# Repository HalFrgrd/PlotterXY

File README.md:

# PlotterXY

- Mainly based on https://github.com/jamescarruthers/PlotteRXY.
- I am using a different main board, y-axis, z-axis. Parts found in onshape.

## How to use
- Open fluidnc in the browser. See https://github.com/HalFrgrd/PlotterXY/blob/main/Firmware/readme.md
- Home all the axes.
- Generate some gcode using vpype. See https://github.com/HalFrgrd/PlotterXY/blob/main/Software/readme.md
- Upload or copy it over to the sd card.
- Plot!

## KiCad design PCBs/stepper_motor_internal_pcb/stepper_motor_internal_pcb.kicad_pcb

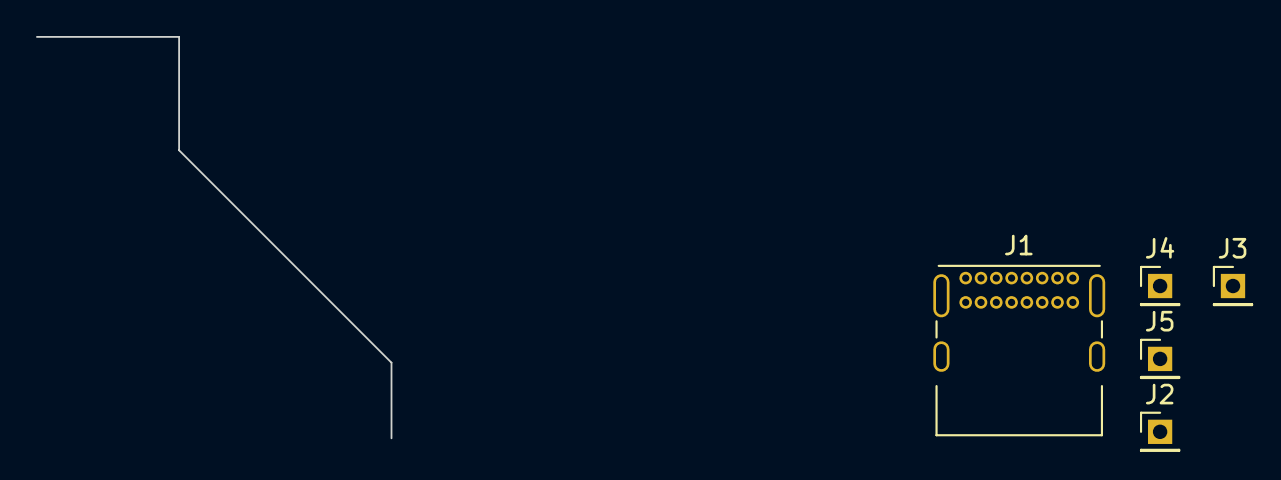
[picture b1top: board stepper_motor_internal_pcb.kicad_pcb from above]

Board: 2 copper layers, 5 parts (0 on the bottom side), 2 nets, no tracks yet.

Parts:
J1: USB_C_Receptacle_USB2.0; USB_C_Receptacle_GCT_USB4085
J2, J3, J4, J5: Conn_01x01_Female; PinHeader_1x01_P2.00mm_Vertical

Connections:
unnamed: J1.A1 (GND), J1.A12 (GND), J1.B1 (GND), J1.B12 (GND)
unnamed: J1.A4 (VBUS), J1.A9 (VBUS), J1.B4 (VBUS), J1.B9 (VBUS)

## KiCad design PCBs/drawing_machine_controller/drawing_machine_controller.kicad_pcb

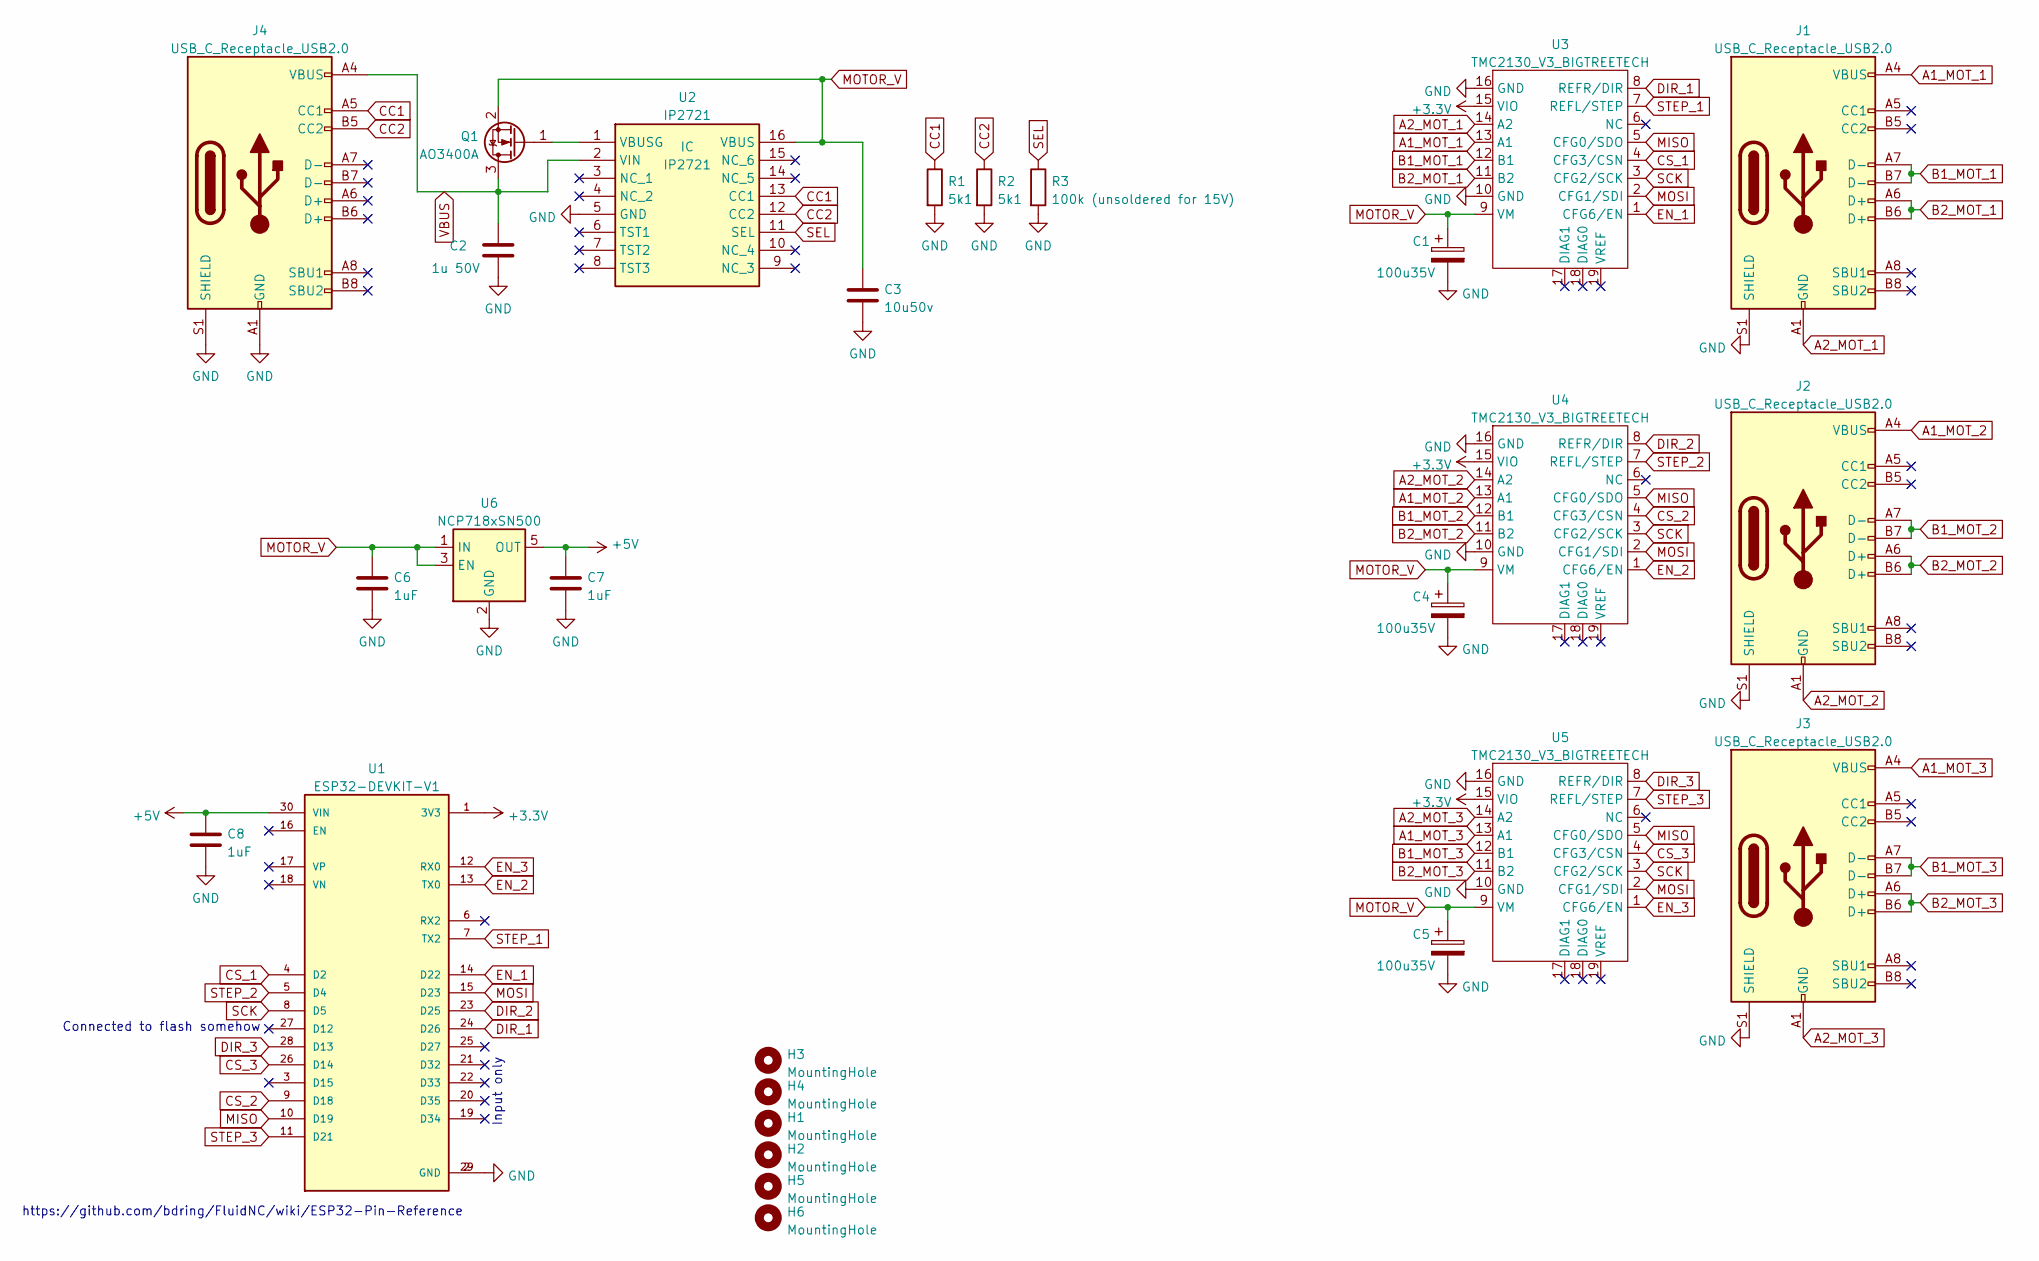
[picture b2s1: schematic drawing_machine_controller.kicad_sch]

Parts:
C1, C4, C5: 100u35V; CP_Elec_8x6.7
C2: 1u 50V; C_0805_2012Metric_Pad1.18x1.45mm_HandSolder
C3: 10u50v; C_0805_2012Metric_Pad1.18x1.45mm_HandSolder
C6, C7, C8: 1uF; C_0805_2012Metric_Pad1.18x1.45mm_HandSolder
H1, H2, H3, H4, H5, H6: MountingHole; MountingHole_5.3mm_M5_Pad_Via
J1, J2, J3, J4: USB_C_Receptacle_USB2.0; USB_C_Receptacle_GCT_USB4085
Q1: AO3400A; SOT-23
R1, R2: 5k1; R_0805_2012Metric_Pad1.20x1.40mm_HandSolder
R3: 100k (unsoldered for 15V); R_0805_2012Metric_Pad1.20x1.40mm_HandSolder
U1: ESP32-DEVKIT-V1; MODULE_ESP32_DEVKIT_V1; PARTREV N/A
U2: IP2721; SOP65P640X120-16N; Manufacturer_Part_Number IP2721
U3, U4, U5: TMC2130_V3_BIGTREETECH
U6: NCP718xSN500; SOT-23-5

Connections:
+3.3V: U1.1 (3V3), U3.15 (VIO), U4.15 (VIO), U5.15 (VIO)
+5V: C7.1, C8.2, U1.30 (VIN), U6.5 (OUT)
A1_MOT_1: J1.A4 (VBUS), J1.A9 (VBUS), J1.B4 (VBUS), J1.B9 (VBUS), U3.13 (A1)
A1_MOT_2: J2.A4 (VBUS), J2.A9 (VBUS), J2.B4 (VBUS), J2.B9 (VBUS), U4.13 (A1)
A1_MOT_3: J3.A4 (VBUS), J3.A9 (VBUS), J3.B4 (VBUS), J3.B9 (VBUS), U5.13 (A1)
A2_MOT_1: J1.A1 (GND), J1.A12 (GND), J1.B1 (GND), J1.B12 (GND), U3.14 (A2)
A2_MOT_2: J2.A1 (GND), J2.A12 (GND), J2.B1 (GND), J2.B12 (GND), U4.14 (A2)
A2_MOT_3: J3.A1 (GND), J3.A12 (GND), J3.B1 (GND), J3.B12 (GND), U5.14 (A2)
B1_MOT_1: J1.A7 (D-), J1.B7 (D-), U3.12 (B1)
B1_MOT_2: J2.A7 (D-), J2.B7 (D-), U4.12 (B1)
B1_MOT_3: J3.A7 (D-), J3.B7 (D-), U5.12 (B1)
B2_MOT_1: J1.A6 (D+), J1.B6 (D+), U3.11 (B2)
B2_MOT_2: J2.A6 (D+), J2.B6 (D+), U4.11 (B2)
B2_MOT_3: J3.A6 (D+), J3.B6 (D+), U5.11 (B2)
CC1: J4.A5 (CC1), R1.1, U2.13 (CC1)
CC2: J4.B5 (CC2), R2.1, U2.12 (CC2)
CS_1: U1.4 (D2), U3.4 (CFG3/CSN)
CS_2: U1.9 (D18), U4.4 (CFG3/CSN)
CS_3: U1.26 (D14), U5.4 (CFG3/CSN)
DIR_1: U1.24 (D26), U3.8 (REFR/DIR)
DIR_2: U1.23 (D25), U4.8 (REFR/DIR)
DIR_3: U1.28 (D13), U5.8 (REFR/DIR)
EN_1: U1.14 (D22), U3.1 (CFG6/EN)
EN_2: U1.13 (TX0), U4.1 (CFG6/EN)
EN_3: U1.12 (RX0), U5.1 (CFG6/EN)
GND: C1.2, C2.2, C3.2, C4.2, C5.2, C6.2, C7.2, C8.1, J1.S1 (SHIELD), J2.S1 (SHIELD), J3.S1 (SHIELD), J4.A1 (GND), J4.A12 (GND), J4.B1 (GND), J4.B12 (GND), J4.S1 (SHIELD), R1.2, R2.2, R3.2, U1.2 (GND), U1.29 (GND), U2.5 (GND), U3.10 (GND), U3.16 (GND), U4.10 (GND), U4.16 (GND), U5.10 (GND), U5.16 (GND), U6.2 (GND)
MISO: U1.10 (D19), U3.5 (CFG0/SDO), U4.5 (CFG0/SDO), U5.5 (CFG0/SDO)
MOSI: U1.15 (D23), U3.2 (CFG1/SDI), U4.2 (CFG1/SDI), U5.2 (CFG1/SDI)
MOTOR_V: C1.1, C3.1, C4.1, C5.1, C6.1, Q1.2 (S), U2.16 (VBUS), U3.9 (VM), U4.9 (VM), U5.9 (VM), U6.1 (IN), U6.3 (EN)
unnamed: Q1.1 (G), U2.1 (VBUSG)
SCK: U1.8 (D5), U3.3 (CFG2/SCK), U4.3 (CFG2/SCK), U5.3 (CFG2/SCK)
SEL: R3.1, U2.11 (SEL)
STEP_1: U1.7 (TX2), U3.7 (REFL/STEP)
STEP_2: U1.5 (D4), U4.7 (REFL/STEP)
STEP_3: U1.11 (D21), U5.7 (REFL/STEP)
VBUS: C2.1, J4.A4 (VBUS), J4.A9 (VBUS), J4.B4 (VBUS), J4.B9 (VBUS), Q1.3 (D), U2.2 (VIN)

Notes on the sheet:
https://github.com/bdring/FluidNC/wiki/ESP32-Pin-Reference
Connected to flash somehow
Input only

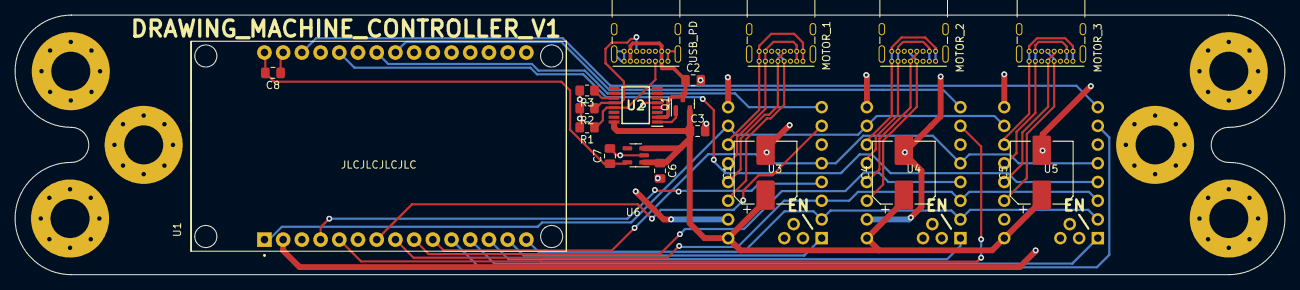
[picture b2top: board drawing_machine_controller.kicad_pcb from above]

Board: 2 copper layers, 172.4 x 35.2 mm, 28 parts (0 on the bottom side), 36 nets.

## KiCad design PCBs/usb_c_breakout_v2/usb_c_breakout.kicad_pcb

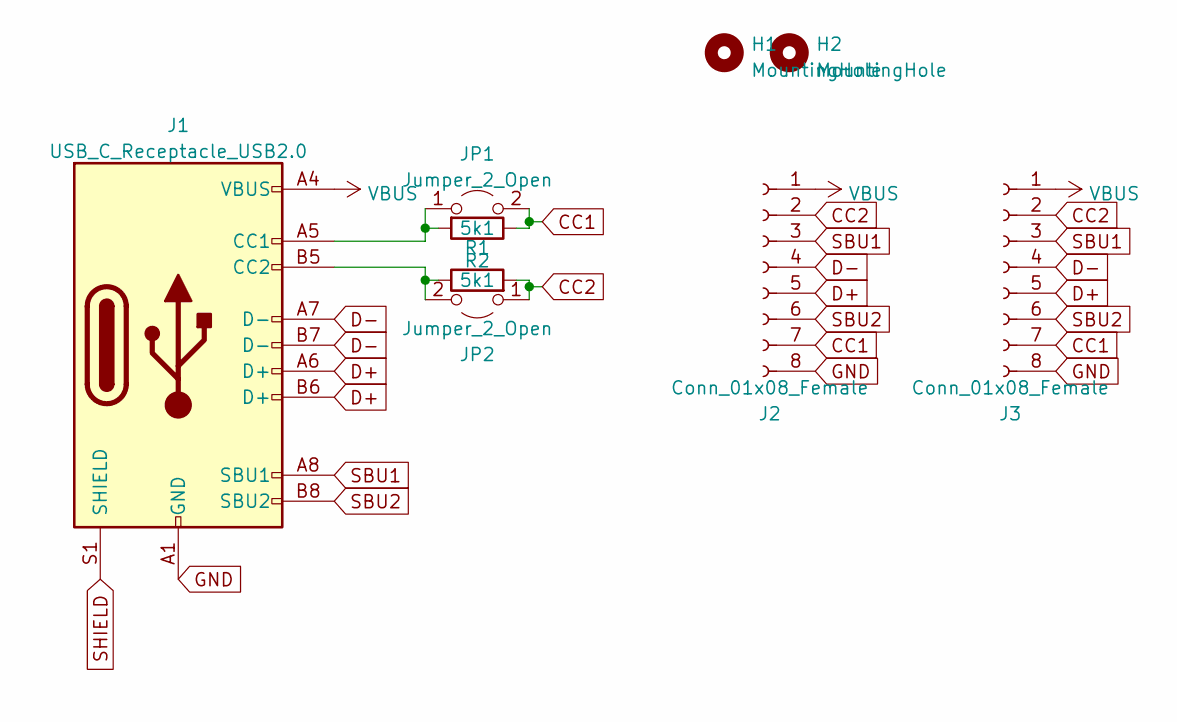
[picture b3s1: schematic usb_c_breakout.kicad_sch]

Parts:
H1, H2: MountingHole; MountingHole_3.2mm_M3_Pad_Via
J1: USB_C_Receptacle_USB2.0; USB_C_Receptacle_GCT_USB4085
J2, J3: Conn_01x08_Female; PinHeader_1x08_P2.54mm_Vertical
JP1, JP2: Jumper_2_Open; SolderJumper-2_P1.3mm_Open_RoundedPad1.0x1.5mm
R1, R2: 5k1; R_0603_1608Metric_Pad0.98x0.95mm_HandSolder

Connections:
CC1: J2.7, J3.7, JP1.2 (B), R1.1
CC2: J2.2, J3.2, JP2.1 (A), R2.2
D+: J1.A6 (D+), J1.B6 (D+), J2.5, J3.5
D-: J1.A7 (D-), J1.B7 (D-), J2.4, J3.4
GND: J1.A1 (GND), J1.A12 (GND), J1.B1 (GND), J1.B12 (GND), J2.8, J3.8
unnamed: J1.A5 (CC1), JP1.1 (A), R1.2
unnamed: J1.B5 (CC2), JP2.2 (B), R2.1
SBU1: J1.A8 (SBU1), J2.3, J3.3
SBU2: J1.B8 (SBU2), J2.6, J3.6
SHIELD: J1.S1 (SHIELD)
VBUS: J1.A4 (VBUS), J1.A9 (VBUS), J1.B4 (VBUS), J1.B9 (VBUS), J2.1, J3.1

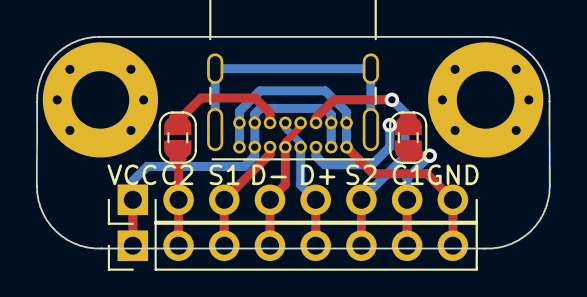
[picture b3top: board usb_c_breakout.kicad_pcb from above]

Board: 2 copper layers, 28.5 x 11.8 mm, 9 parts (0 on the bottom side), 10 nets.

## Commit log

2023-05-11 gitignore
2023-05-11 pcbs
2023-06-03 pcb tweak, fluidnc start
2023-07-23 basic config
2023-11-16 new chinese board
2023-11-22 got homing working
2023-12-02 first drawing
2023-12-05 software
2023-12-05 calibrating
2023-12-21 maze
2023-12-23 donut
2023-12-23 contour lines
2023-12-24 basic contours
2023-12-24 tidying up
2023-12-24 optimizations
2023-12-28 contout optimizations
2023-12-29 optimizations and osm
2023-12-30 maxe working with shapely
2023-12-30 cleaning up
2023-12-30 torus rendering
2023-12-30 meta torus
2024-01-01 deformed circles
2024-05-11 line heights
2024-05-11 3d square columns
2024-05-12 :asd:
2025-09-13 vscode
